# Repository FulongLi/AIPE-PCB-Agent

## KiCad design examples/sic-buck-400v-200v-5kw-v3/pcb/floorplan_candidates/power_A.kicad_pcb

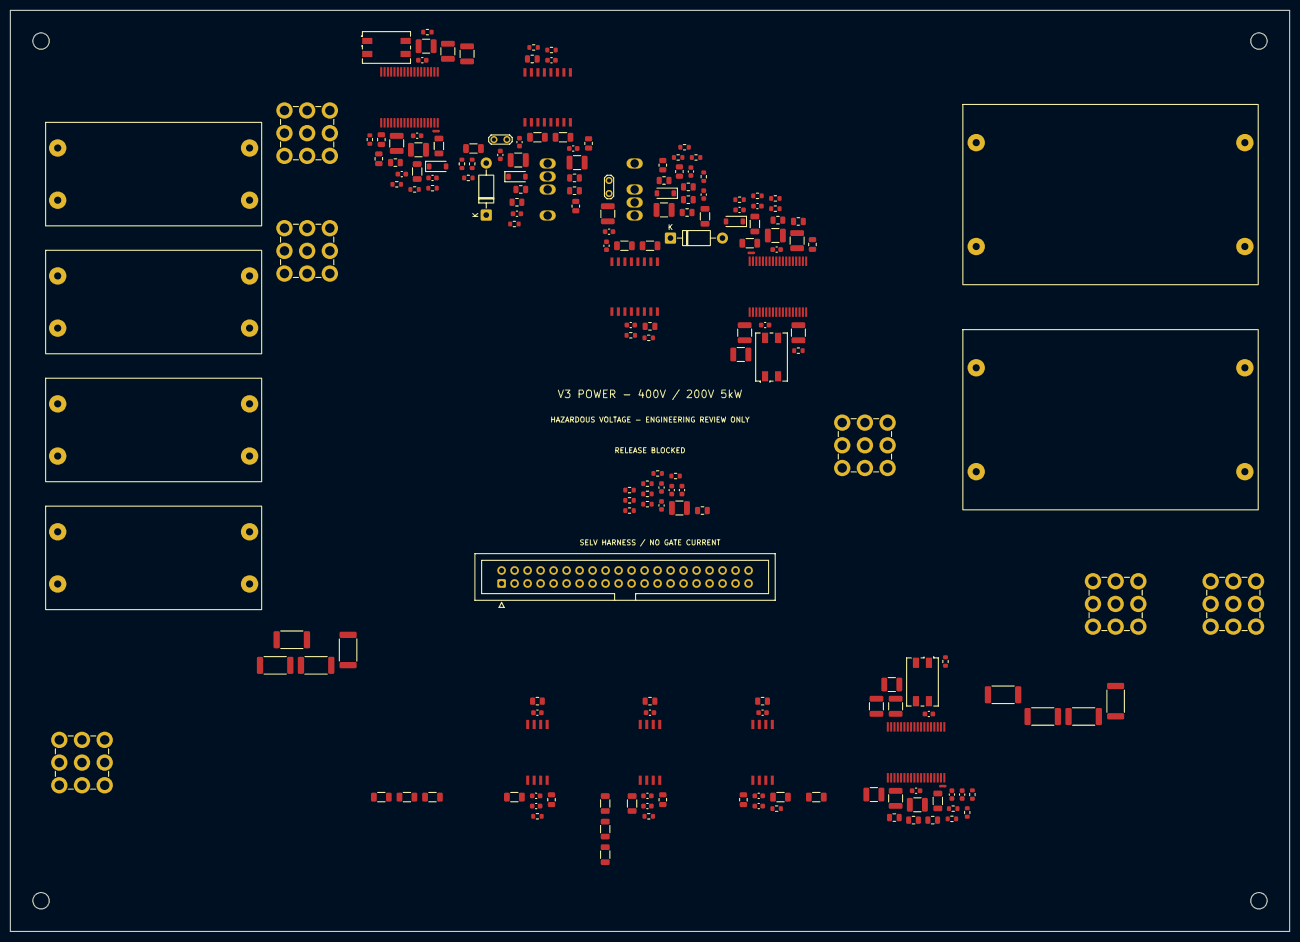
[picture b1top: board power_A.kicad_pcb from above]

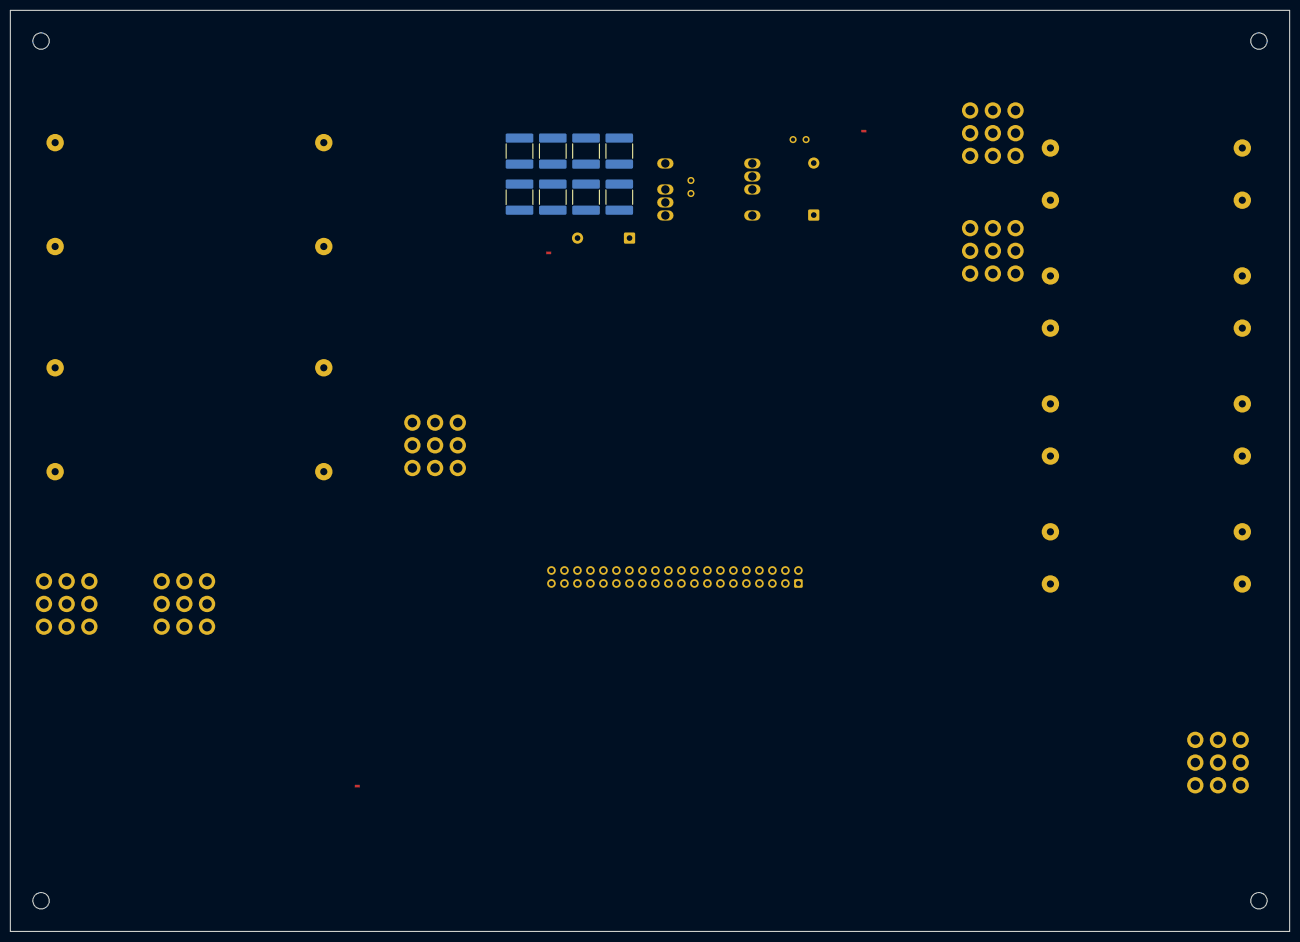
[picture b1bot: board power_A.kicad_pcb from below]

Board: 4 copper layers, 250.0 x 180.0 mm, 202 parts (8 on the bottom side), 89 nets, no tracks yet.

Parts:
C1, C2, C3, C4: 15u / 900V; V3_CIN_15U
C5, C6, C7, C8, C9, C10, C11, C12: 0.47u/630V; C_2220_5750Metric
C13, C14: 100u / 450V; V3_COUT_100U
C15, C16, C17, C18, C24, C27, C28, C29, C30, C36, C45, C46, C47, C57, C58, C59, C65, C67, C70, C72, C75, C77, C84, C85, C86, C96: 1u/50V; C_0805_2012Metric
C19, C20, C31, C32, C39, C40, C41, C51, C52, C53, C78, C79, C80, C90, C95: 10u/25V; C_1210_3225Metric
C21, C22, C23, C33, C34, C35, C42, C50, C54, C62, C64, C66, C69, C71, C74, C76, C81, C89: 100n/50V; C_0603_1608Metric
C25, C37, C63, C68, C73: 1n/50V; C_0603_1608Metric
C26, C38: 680p/50V; C_0603_1608Metric
C43, C44, C55, C56, C82, C83: 330p/50V; C_0603_1608Metric
C48, C49, C60, C61, C87, C88: 10u/50V; C_1210_3225Metric
C91, C92, C93, C94: 100p/50V; C_0603_1608Metric
D1, D3: UF4007-E3/54; D_DO-41_SOD81_P10.16mm_Horizontal
D2, D4, D5, D6: BAT46W-E3-08; D_SOD-123
H1, H2, H3, H4: M3 insulated standoff; MountingHole_3.2mm_M3
J1: INPUT LINK +; Wuerth_REDCUBE-THR_WP-THRSH_74651195_THR
J2: INPUT / OUTPUT RETURN; Wuerth_REDCUBE-THR_WP-THRSH_74651195_THR
J3: SW TO CHOKE; Wuerth_REDCUBE-THR_WP-THRSH_74651195_THR
J4: CHOKE RETURN / OUTPUT +; Wuerth_REDCUBE-THR_WP-THRSH_74651195_THR
J5: OUTPUT RETURN; Wuerth_REDCUBE-THR_WP-THRSH_74651195_THR
J6: RAW INPUT SENSE; Wuerth_REDCUBE-THR_WP-THRSH_74651195_THR
J7: POWER / CONTROL — 40-way; IDC-Header_2x20_P2.54mm_Vertical
L2, L3, L4: 744226S; L_CommonMode_Wuerth_WE-SL2
NT1, NT2, NT3: VEEA STAR; NetTie-2_SMD_Pad0.5mm
Q1, Q2: C4MS025120K; V3_TO247_4
R1, R2, R3, R4: 91k; R_2512_6332Metric
R5, R6, R7, R8: 43k; R_2512_6332Metric
R9, R19: 10; R_1206_3216Metric
R10, R20: 3.3; R_1206_3216Metric
R11, R21: 10k; R_0805_2012Metric
R12, R22: 3.3k; R_0603_1608Metric
R13, R23: 20k; R_0603_1608Metric
R14, R15, R24, R25, R35, R42, R61: 4.7k; R_0603_1608Metric
R16, R26: 2.2k; R_1206_3216Metric
R17, R27: 9.09k; R_0603_1608Metric
R18, R28: 1k; R_0603_1608Metric
R29, R36: 121k; R_0603_1608Metric
R30, R32, R37, R39, R57, R58, R59: 16.2k; R_0603_1608Metric
R31, R38: 9.76k; R_0603_1608Metric
R33, R40: 1k; R_1206_3216Metric
R34, R41: 180; R_1206_3216Metric
R43, R44, R45, R46, R48, R49, R50, R51, R53, R54: 750k; R_1206_3216Metric
R47, R52, R55, R63, R65, R67, R69: 10k; R_0603_1608Metric
R56: 87.6k; R_0603_1608Metric
R60: 82; R_1206_3216Metric
R62, R64, R66, R68: 33; R_0603_1608Metric
RT1, RT2: 10k NTC B3988; R_0805_2012Metric
TP1: VGS H; TestPoint_2Pads_Pitch2.54mm_Drill0.8mm
TP2: VGS L; TestPoint_2Pads_Pitch2.54mm_Drill0.8mm
U1, U2: UCC21710QDWRQ1; V3_UCC21710_HV
U3, U4, U8: UCC14141QDWNRQ1; V3_UCC14141_DWN
U5, U6, U7: AMC1311BDWVR; V3_AMC1311_DWV

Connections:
3V3: C23.1, C24.1, C35.1, C36.1, C66.1, C67.1, C71.1, C72.1, C76.1, C77.1, C96.1, J7.37, J7.38, R14.1, R15.1, R24.1, R25.1, R35.1, R42.1, R61.1, U1.15, U2.15, U5.8, U6.8, U7.8
12V_E: C95.1, J7.33, J7.34, L2.1, L3.1, L4.1
12V_H_BIAS: C39.1, C40.1, C41.1, C42.1, L2.4, U3.6, U3.7
12V_L_BIAS: C51.1, C52.1, C53.1, C54.1, L3.4, U4.6, U4.7
12V_S_BIAS: C78.1, C79.1, C80.1, C81.1, L4.4, U8.6, U8.7
BIAS_EN: J7.8, R68.1
BIAS_EN_F: C94.1, R68.2, R69.1, U3.4, U4.4, U8.4
BLEED_IN_1: R1.2, R2.1
BLEED_IN_2: R2.2, R3.1
BLEED_IN_3: R3.2, R4.1
BLEED_OUT_1: R5.2, R6.1
BLEED_OUT_2: R6.2, R7.1
BLEED_OUT_3: R7.2, R8.1
BUS: C1.1, C2.1, C3.1, C4.1, C5.1, C6.1, C7.1, C8.1, C9.1, C10.1, C11.1, C12.1, D1.1, J1.1, Q1.1, R1.1, R48.1
BUS_ADCIN: C68.1, R51.2, R52.1, U6.2
BUS_DIV1: R48.2, R49.1
BUS_DIV2: R49.2, R50.1
BUS_DIV3: R50.2, R51.1
BUS_N: J7.26, U6.6
BUS_P: J7.25, U6.7
DESAT_H: D1.2, R16.2, R17.1
DESAT_L: D3.2, R26.2, R27.1
DRV_RESET: J7.6, R66.1
DRV_RESET_F: C93.1, R66.2, R67.1, U1.14, U2.14
FLT_H_N: J7.10, R15.2, U1.13
FLT_L_N: J7.12, R25.2, U2.13
GNDP_H: C39.2, C40.2, C41.2, C42.2, L2.3, U3.1, U3.2, U3.5, U3.8, U3.9, U3.10, U3.11, U3.12, U3.13, U3.14, U3.15, U3.16, U3.17, U3.18
GNDP_L: C51.2, C52.2, C53.2, C54.2, L3.3, U4.1, U4.2, U4.5, U4.8, U4.9, U4.10, U4.11, U4.12, U4.13, U4.14, U4.15, U4.16, U4.17, U4.18
GNDP_S: C78.2, C79.2, C80.2, C81.2, L4.3, U8.1, U8.2, U8.5, U8.8, U8.9, U8.10, U8.11, U8.12, U8.13, U8.14, U8.15, U8.16, U8.17, U8.18
GND_CTRL: C23.2, C24.2, C35.2, C36.2, C66.2, C67.2, C71.2, C72.2, C76.2, C77.2, C91.2, C92.2, C93.2, C94.2, C95.2, C96.2, J7.1, J7.3, J7.5, J7.7, J7.9, J7.11, J7.13, J7.15, J7.17, J7.19, J7.21, J7.29, J7.31, J7.35, J7.36, J7.39, J7.40, L2.2, L3.2, L4.2, R63.2, R65.2, R67.2, R69.2, U1.9, U2.9, U5.5, U6.5, U7.5
G_H: Q1.4, R9.2, R10.2, R11.1, TP1.1, U1.7
G_L: Q2.4, R19.2, R20.2, R21.1, TP2.1, U2.7
H_FBVDD: C43.1, R29.2, R30.1, U3.34
H_FBVEE: C44.1, R31.2, R32.1, U3.33
H_RDR: D5.1, R34.2
H_RLIM: R33.1, R34.1, U3.32
H_VEEA: C43.2, C44.2, NT1.1, R30.2, R32.2, U3.35
KS_H: C15.2, C16.2, C17.2, C18.2, C19.1, C20.1, C21.2, C22.1, C25.2, C26.2, D2.2, D5.2, Q1.3, R11.2, R13.2, R18.2, R31.1, R33.2, RT1.2, TP1.2, U1.3
KS_L: C27.2, C28.2, C29.2, C30.2, C31.1, C32.1, C33.2, C34.1, C37.2, C38.2, D4.2, D6.2, Q2.3, R21.2, R23.2, R28.2, R38.1, R40.2, RT2.2, TP2.2, U2.3
L_FBVDD: C55.1, R36.2, R37.1, U4.34
L_FBVEE: C56.1, R38.2, R39.1, U4.33
L_RDR: D6.1, R41.2
L_RLIM: R40.1, R41.1, U4.32
L_VEEA: C55.2, C56.2, NT2.1, R37.2, R39.2, U4.35
NTC_H: C25.1, R12.1, R13.1, U1.1
NTC_L: C37.1, R22.1, R23.1, U2.1
NTC_R_H: R12.2, RT1.1
NTC_R_L: R22.2, RT2.1
OC_H: C26.1, D2.1, R17.2, R18.1, U1.2
OC_L: C38.1, D4.1, R27.2, R28.1, U2.2
OUTH_H: R9.1, U1.4
OUTH_L: R19.1, U2.4
OUTL_H: R10.1, U1.6
OUTL_L: R20.1, U2.6
OUT_ADCIN: C73.1, R54.2, R55.1, U7.2
OUT_DIV1: R53.2, R54.1
OUT_N: J7.28, U7.6
OUT_P: J7.27, U7.7
PGND: C1.2, C2.2, C3.2, C4.2, C5.2, C6.2, C7.2, C8.2, C9.2, C10.2, C11.2, C12.2, C13.2, C14.2, C63.2, C64.2, C65.2, C68.2, C69.2, C70.2, C73.2, C74.2, C75.2, C84.2, C85.2, C86.2, C87.2, C88.2, C89.2, C90.2, J2.1, J5.1, NT3.2, Q2.2, R4.2, R8.2, R47.2, R52.2, R55.2, U5.3, U5.4, U6.3, U6.4, U7.3, U7.4, U8.19, U8.20, U8.21, U8.22, U8.23, U8.24, U8.25, U8.26, U8.27, U8.30, U8.31, U8.36
PG_H_N: J7.18, R35.2, U3.3
PG_L_N: J7.20, R42.2, U4.3
PG_S_N: J7.22, R61.2, U8.3
PWM_H: J7.2, R62.1
PWM_H_F: C91.1, R62.2, R63.1, U1.10, U2.11
PWM_L: J7.4, R64.1
PWM_L_F: C92.1, R64.2, R65.1, U1.11, U2.10
RAW: J6.1, R43.1
RAW_ADCIN: C63.1, R46.2, R47.1, U5.2
RAW_DIV1: R43.2, R44.1
RAW_DIV2: R44.2, R45.1
RAW_DIV3: R45.2, R46.1
RAW_N: J7.24, U5.6
RAW_P: J7.23, U5.7
RDY_H: J7.14, R14.2, U1.12
RDY_L: J7.16, R24.2, U2.12
SW: D3.1, J3.1, Q1.2, Q2.1
S_5V: C64.1, C65.1, C69.1, C70.1, C74.1, C75.1, C90.1, R58.1, R60.2, U5.1, U6.1, U7.1
S_16V: C84.1, C85.1, C86.1, C87.1, C88.1, C89.1, R56.1, U8.28, U8.29
S_FBVDD: C82.1, R56.2, R57.1, U8.34
S_FBVEE: C83.1, R58.2, R59.1, U8.33
S_RLIM: R60.1, U8.32
S_VEEA: C82.2, C83.2, NT3.1, R57.2, R59.2, U8.35
TH_H_PWM: J7.30, U1.16
TH_L_PWM: J7.32, U2.16
VDD_H: C15.1, C16.1, C17.1, C18.1, C21.1, C45.1, C46.1, C47.1, C48.1, C49.1, C50.1, R16.1, R29.1, U1.5, U3.28, U3.29
VDD_L: C27.1, C28.1, C29.1, C30.1, C33.1, C57.1, C58.1, C59.1, C60.1, C61.1, C62.1, R26.1, R36.1, U2.5, U4.28, U4.29
VEE_H: C19.2, C20.2, C22.2, C45.2, C46.2, C47.2, C48.2, C49.2, C50.2, NT1.2, U1.8, U3.19, U3.20, U3.21, U3.22, U3.23, U3.24, U3.25, U3.26, U3.27, U3.30, U3.31, U3.36
VEE_L: C31.2, C32.2, C34.2, C57.2, C58.2, C59.2, C60.2, C61.2, C62.2, NT2.2, U2.8, U4.19, U4.20, U4.21, U4.22, U4.23, U4.24, U4.25, U4.26, U4.27, U4.30, U4.31, U4.36
VOUT: C13.1, C14.1, J4.1, R5.1, R53.1
